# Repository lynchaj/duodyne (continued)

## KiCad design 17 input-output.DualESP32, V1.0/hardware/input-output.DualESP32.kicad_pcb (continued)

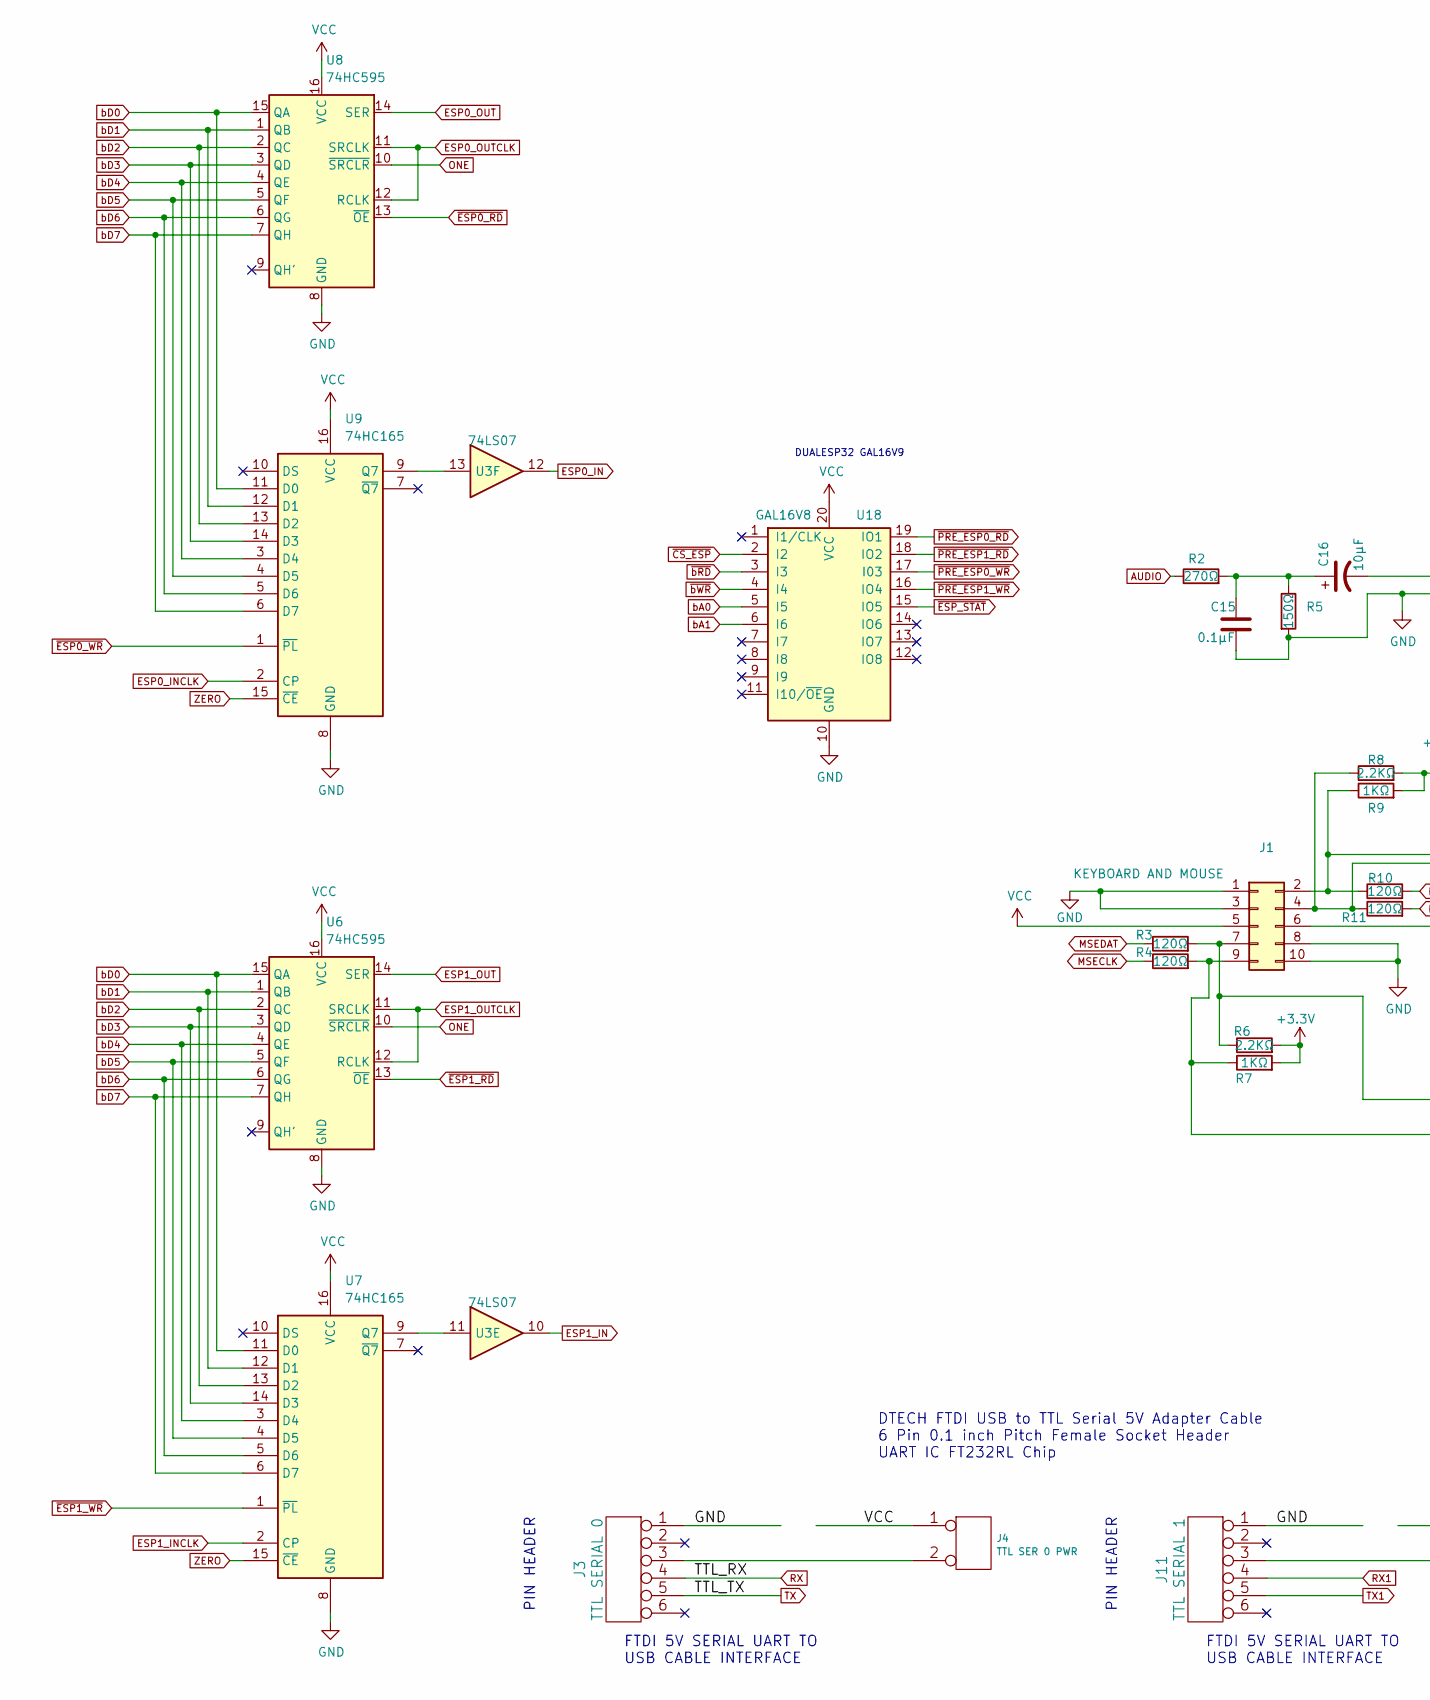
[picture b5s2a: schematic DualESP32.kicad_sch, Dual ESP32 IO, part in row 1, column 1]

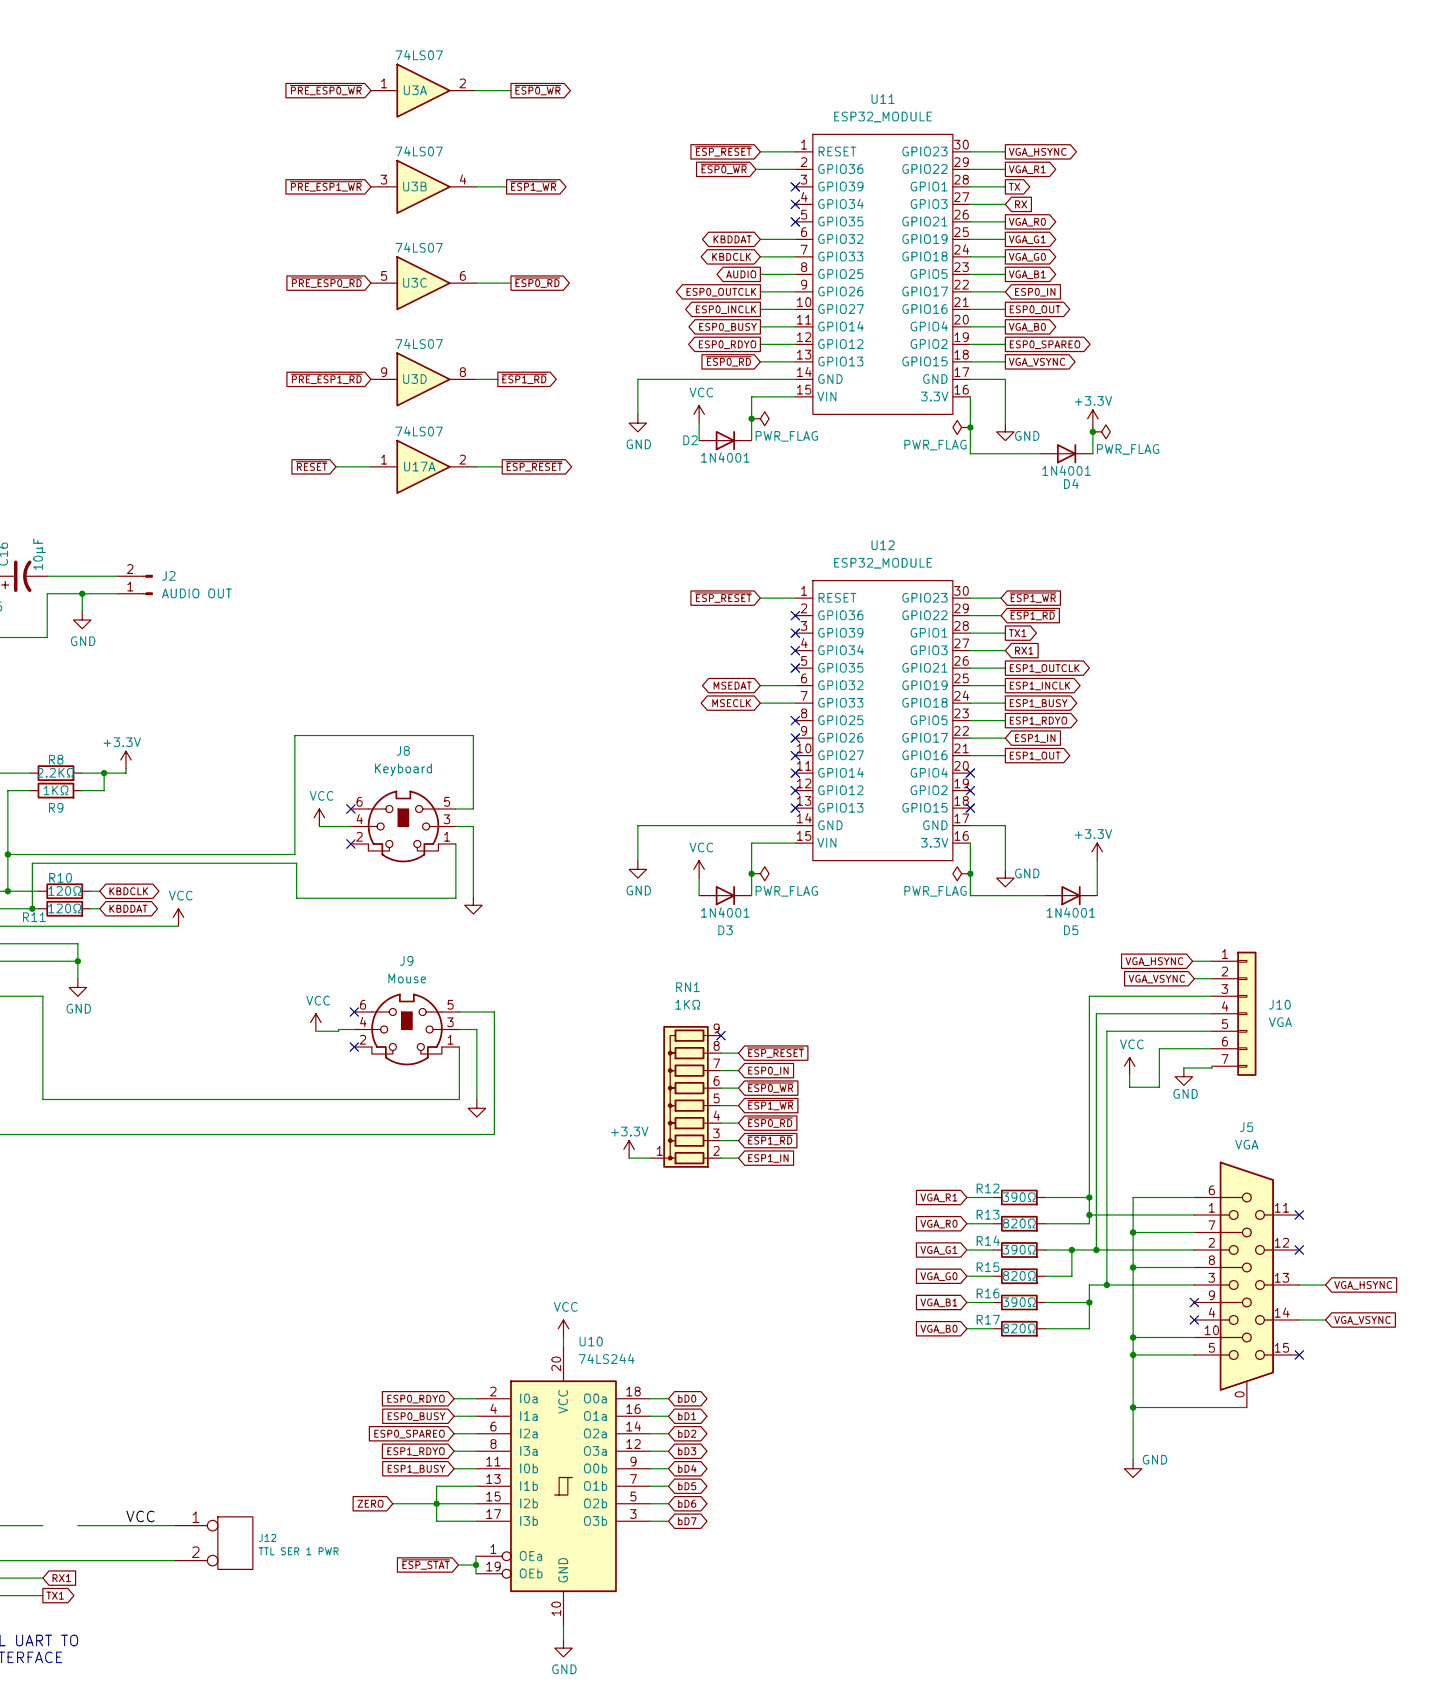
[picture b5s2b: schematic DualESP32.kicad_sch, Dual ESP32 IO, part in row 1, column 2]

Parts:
C15: 0.1µF; C_Disc_D5.0mm_W2.5mm_P5.00mm
C16: 10µF; CP_Radial_D5.0mm_P2.50mm
D2, D3, D4, D5: 1N4001; D_DO-41_SOD81_P10.16mm_Horizontal
J1: KEYBOARD AND MOUSE; PinHeader_2x05_P2.54mm_Horizontal
J2: AUDIO OUT; PinHeader_1x02_P2.54mm_Horizontal
J3: TTL SERIAL 0; PinHeader_1x06_P2.54mm_Horizontal
J4: TTL SER 0 PWR; PinHeader_1x02_P2.54mm_Vertical
J5: VGA; DSUB-15-HD_Female_Horizontal_P2.29x1.98mm_EdgePinOffset3.03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
J8: Keyboard; mini_din
J9: Mouse; mini_din
J10: VGA; PinHeader_1x07_P2.54mm_Horizontal
J11: TTL SERIAL 1; PinHeader_1x06_P2.54mm_Horizontal
J12: TTL SER 1 PWR; PinHeader_1x02_P2.54mm_Vertical
R2: 270Ω; R_Axial_DIN0207_L6.3mm_D2.5mm_P7.62mm_Horizontal
R3, R4, R10, R11: 120Ω; R_Axial_DIN0207_L6.3mm_D2.5mm_P7.62mm_Horizontal
R5: 150Ω; R_Axial_DIN0207_L6.3mm_D2.5mm_P7.62mm_Horizontal
R6, R8: 2.2KΩ; R_Axial_DIN0207_L6.3mm_D2.5mm_P7.62mm_Horizontal
R7, R9: 1KΩ; R_Axial_DIN0207_L6.3mm_D2.5mm_P7.62mm_Horizontal
R12, R14, R16: 390Ω; R_Axial_DIN0207_L6.3mm_D2.5mm_P7.62mm_Horizontal
R13, R15, R17: 820Ω; R_Axial_DIN0207_L6.3mm_D2.5mm_P7.62mm_Horizontal
RN1: 1KΩ; R_Array_SIP9
U3, U17: 74LS07; DIP-14_W7.62mm
U6, U8: 74HC595; DIP-16_W7.62mm
U7, U9: 74HC165; DIP-16_W7.62mm
U10: 74LS244; DIP-20_W7.62mm
U11, U12: ESP32_MODULE
U18: GAL16V8; DIP-20_W7.62mm

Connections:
+3.3V: D4.1 (K), D5.1 (K), R6.2, R7.2, R8.2, R9.2, RN1.1 (common)
AUDIO: R2.1, U11.8 (GPIO25)
ESP0_BUSY: U10.4 (I1a), U11.11 (GPIO14)
ESP0_IN: RN1.7 (R6), U3.12, U11.22 (GPIO17)
ESP0_INCLK: U9.2 (CP), U11.10 (GPIO27)
ESP0_OUT: U8.14 (SER), U11.21 (GPIO16)
ESP0_OUTCLK: U8.11 (SRCLK), U8.12 (RCLK), U11.9 (GPIO26)
ESP0_RDYO: U10.2 (I0a), U11.12 (GPIO12)
ESP0_SPAREO: U10.6 (I2a), U11.19 (GPIO2)
ESP1_BUSY: U10.11 (I0b), U12.24 (GPIO18)
ESP1_IN: RN1.2 (R1), U3.10, U12.22 (GPIO17)
ESP1_INCLK: U7.2 (CP), U12.25 (GPIO19)
ESP1_OUT: U6.14 (SER), U12.21 (GPIO16)
ESP1_OUTCLK: U6.11 (SRCLK), U6.12 (RCLK), U12.26 (GPIO21)
ESP1_RDYO: U10.8 (I3a), U12.23 (GPIO5)
GND: C15.2, J1.1, J1.3, J1.8, J1.10, J2.1, J3.1, J5.0, J5.5, J5.6, J5.7, J5.8, J5.10, J8.3, J8.SH1, J8.SH2, J8.SH3, J9.3, J9.SH1, J9.SH2, J9.SH3, J10.7, J11.1, R5.2, U6.8 (GND), U7.8 (GND), U8.8 (GND), U9.8 (GND), U10.10 (GND), U11.14 (GND), U11.17 (GND), U12.14 (GND), U12.17 (GND), U18.10 (GND); also elsewhere on the board
KBDCLK: R10.2, U11.7 (GPIO33)
KBDDAT: R11.2, U11.6 (GPIO32)
MSECLK: R4.1, U12.7 (GPIO33)
MSEDAT: R3.1, U12.6 (GPIO32)
unnamed: C15.1, C16.1, R2.2, R5.1
unnamed: C16.2, J2.2
unnamed: D2.1 (K), U11.15 (VIN)
unnamed: D3.1 (K), U12.15 (VIN)
unnamed: D4.2 (A), U11.16 (3.3V)
unnamed: D5.2 (A), U12.16 (3.3V)
unnamed: J1.2, J8.5, R9.1, R10.1
unnamed: J1.4, J8.1, R8.1, R11.1
unnamed: J1.7, J9.1, R3.2, R6.1
unnamed: J1.9, J9.5, R4.2, R7.1
unnamed: J3.3, J4.2 (PM)
unnamed: J5.1, J10.3, R12.2, R13.2
unnamed: J5.2, J10.4, R14.2, R15.2
unnamed: J5.3, J10.5, R16.2, R17.2
unnamed: J11.3, J12.2 (PM)
unnamed: U3.11, U7.9 (Q7)
unnamed: U3.13, U9.9 (Q7)
ONE: U6.10 (~SRCLR), U8.10 (~SRCLR); also elsewhere on the board
RX: J3.4, U11.27 (GPIO3)
RX1: J11.4, U12.27 (GPIO3)
TX: J3.5, U11.28 (GPIO1)
TX1: J11.5, U12.28 (GPIO1)
VCC: D2.2 (A), D3.2 (A), J1.5, J1.6, J4.1, J8.4, J9.4, J10.6, J12.1, U6.16 (VCC), U7.16 (VCC), U8.16 (VCC), U9.16 (VCC), U10.20 (VCC), U18.20 (VCC); also elsewhere on the board
VGA_B0: R17.1, U11.20 (GPIO4)
VGA_B1: R16.1, U11.23 (GPIO5)
VGA_G0: R15.1, U11.24 (GPIO18)
VGA_G1: R14.1, U11.25 (GPIO19)
VGA_HSYNC: J5.13, J10.1, U11.30 (GPIO23)
VGA_R0: R13.1, U11.26 (GPIO21)
VGA_R1: R12.1, U11.29 (GPIO22)
VGA_VSYNC: J5.14, J10.2, U11.18 (GPIO15)
ZERO: U7.15 (~CE), U9.15 (~CE), U10.13 (I1b), U10.15 (I2b), U10.17 (I3b); also elsewhere on the board
bA0: U18.5 (I5); also elsewhere on the board
bA1: U18.6 (I6); also elsewhere on the board
bD0: U6.15 (QA), U7.11 (D0), U8.15 (QA), U9.11 (D0), U10.18 (O0a); also elsewhere on the board
bD1: U6.1 (QB), U7.12 (D1), U8.1 (QB), U9.12 (D1), U10.16 (O1a); also elsewhere on the board
bD2: U6.2 (QC), U7.13 (D2), U8.2 (QC), U9.13 (D2), U10.14 (O2a); also elsewhere on the board
bD3: U6.3 (QD), U7.14 (D3), U8.3 (QD), U9.14 (D3), U10.12 (O3a); also elsewhere on the board
bD4: U6.4 (QE), U7.3 (D4), U8.4 (QE), U9.3 (D4), U10.9 (O0b); also elsewhere on the board
bD5: U6.5 (QF), U7.4 (D5), U8.5 (QF), U9.4 (D5), U10.7 (O1b); also elsewhere on the board
bD6: U6.6 (QG), U7.5 (D6), U8.6 (QG), U9.5 (D6), U10.5 (O2b); also elsewhere on the board
bD7: U6.7 (QH), U7.6 (D7), U8.7 (QH), U9.6 (D7), U10.3 (O3b); also elsewhere on the board
~CS_ESP: U18.2 (I2); also elsewhere on the board
~ESP0_RD: RN1.4 (R3), U3.6, U8.13 (~OE), U11.13 (GPIO13)
~ESP0_WR: RN1.6 (R5), U3.2, U9.1 (~PL), U11.2 (GPIO36)
~ESP1_RD: RN1.3 (R2), U3.8, U6.13 (~OE), U12.29 (GPIO22)
~ESP1_WR: RN1.5 (R4), U3.4, U7.1 (~PL), U12.30 (GPIO23)
~ESP_RESET: RN1.8 (R7), U11.1 (RESET), U12.1 (RESET), U17.2
~ESP_STAT: U10.1 (OEa), U10.19 (OEb), U18.15 (IO5)
~PRE_ESP0_RD: U3.5, U18.19 (IO1)
~PRE_ESP0_WR: U3.1, U18.17 (I03)
~PRE_ESP1_RD: U3.9, U18.18 (IO2)
~PRE_ESP1_WR: U3.3, U18.16 (IO4)
~RESET: U17.1; also elsewhere on the board
~bRD: U18.3 (I3); also elsewhere on the board
~bWR: U18.4 (I4); also elsewhere on the board

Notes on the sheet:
FTDI 5V SERIAL UART TO USB CABLE INTERFACE
PIN HEADER
DTECH FTDI USB to TTL Serial 5V Adapter Cable 6 Pin 0.1 inch Pitch Female Socket Header UART IC FT232RL Chip
DUALESP32 GAL16V9

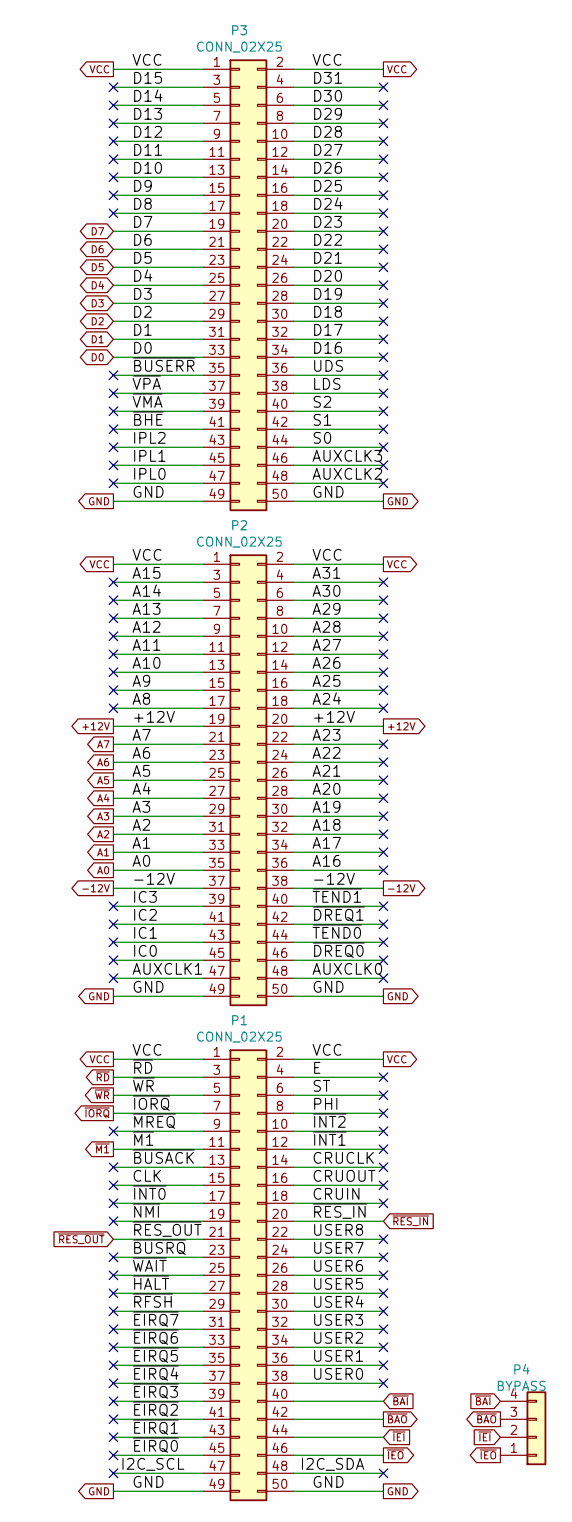
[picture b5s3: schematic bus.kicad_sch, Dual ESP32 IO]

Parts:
P1, P2, P3: CONN_02X25; IDC-Header_2x25_P2.54mm_Horizontal
P4: BYPASS; PinHeader_1x04_P2.54mm_Vertical

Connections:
+12V: P2.19, P2.20
-12V: P2.37, P2.38
/bus/A8: P2.17
/bus/A9: P2.15
/bus/A10: P2.13
/bus/A11: P2.11
/bus/A12: P2.9
/bus/A13: P2.7
/bus/A14: P2.5
/bus/A15: P2.3
/bus/A16: P2.36
/bus/A17: P2.34
/bus/A18: P2.32
/bus/A19: P2.30
/bus/A20: P2.28
/bus/A21: P2.26
/bus/A22: P2.24
/bus/A23: P2.22
/bus/A24: P2.18
/bus/A25: P2.16
/bus/A26: P2.14
/bus/A27: P2.12
/bus/A28: P2.10
/bus/A29: P2.8
/bus/A30: P2.6
/bus/A31: P2.4
/bus/AUXCLK0: P2.48
/bus/AUXCLK1: P2.47
/bus/AUXCLK2: P3.48
/bus/AUXCLK3: P3.46
/bus/CLK: P1.15
/bus/CRUCLK: P1.14
/bus/CRUIN: P1.18
/bus/CRUOUT: P1.16
/bus/D8: P3.17
/bus/D9: P3.15
/bus/D10: P3.13
/bus/D11: P3.11
/bus/D12: P3.9
/bus/D13: P3.7
/bus/D14: P3.5
/bus/D15: P3.3
/bus/D16: P3.34
/bus/D17: P3.32
/bus/D18: P3.30
/bus/D19: P3.28
/bus/D20: P3.26
/bus/D21: P3.24
/bus/D22: P3.22
/bus/D23: P3.20
/bus/D24: P3.18
/bus/D25: P3.16
/bus/D26: P3.14
/bus/D27: P3.12
/bus/D28: P3.10
/bus/D29: P3.8
/bus/D30: P3.6
/bus/D31: P3.4
/bus/E: P1.4
/bus/I2C_SCL: P1.47
/bus/I2C_SDA: P1.48
/bus/IC0: P2.45
/bus/IC1: P2.43
/bus/IC2: P2.41
/bus/IC3: P2.39
/bus/IPL0: P3.47
/bus/IPL1: P3.45
/bus/IPL2: P3.43
/bus/LDS: P3.38
/bus/PHI: P1.8
/bus/S0: P3.44
/bus/S1: P3.42
/bus/S2: P3.40
/bus/ST: P1.6
/bus/UDS: P3.36
/bus/USER0: P1.38
/bus/USER1: P1.36
/bus/USER2: P1.34
/bus/USER3: P1.32
/bus/USER4: P1.30
/bus/USER5: P1.28
/bus/USER6: P1.26
/bus/USER7: P1.24
/bus/USER8: P1.22
/bus/~BHE: P3.41
/bus/~BUSACK: P1.13
/bus/~BUSERR: P3.35
/bus/~BUSRQ: P1.23
/bus/~DREQ0: P2.46
/bus/~DREQ1: P2.42
/bus/~EIRQ0: P1.45
/bus/~EIRQ1: P1.43
/bus/~EIRQ2: P1.41
/bus/~EIRQ3: P1.39
/bus/~EIRQ4: P1.37
/bus/~EIRQ5: P1.35
/bus/~EIRQ6: P1.33
/bus/~EIRQ7: P1.31
/bus/~HALT: P1.27
/bus/~INT0: P1.17
/bus/~INT1: P1.12
/bus/~INT2: P1.10
/bus/~MREQ: P1.9
/bus/~NMI: P1.19
/bus/~RFSH: P1.29
/bus/~TEND0: P2.44
/bus/~TEND1: P2.40
/bus/~VMA: P3.39
/bus/~VPA: P3.37
/bus/~WAIT: P1.25
A0: P2.35; also elsewhere on the board
A1: P2.33; also elsewhere on the board
A2: P2.31; also elsewhere on the board
A3: P2.29; also elsewhere on the board
A4: P2.27; also elsewhere on the board
A5: P2.25; also elsewhere on the board
A6: P2.23; also elsewhere on the board
A7: P2.21; also elsewhere on the board
D0: P3.33; also elsewhere on the board
D1: P3.31; also elsewhere on the board
D2: P3.29; also elsewhere on the board
D3: P3.27; also elsewhere on the board
D4: P3.25; also elsewhere on the board
D5: P3.23; also elsewhere on the board
D6: P3.21; also elsewhere on the board
D7: P3.19; also elsewhere on the board
GND: P1.49, P1.50, P2.49, P2.50, P3.49, P3.50; also elsewhere on the board
VCC: P1.1, P1.2, P2.1, P2.2, P3.1, P3.2; also elsewhere on the board
~BAI: P1.40, P4.4
~BAO: P1.42, P4.3
~IEI: P1.44, P4.2
~IEO: P1.46, P4.1
~IORQ: P1.7; also elsewhere on the board
~M1: P1.11; also elsewhere on the board
~RD: P1.3; also elsewhere on the board
~RES_IN: P1.20; also elsewhere on the board
~RES_OUT: P1.21; also elsewhere on the board
~WR: P1.5; also elsewhere on the board

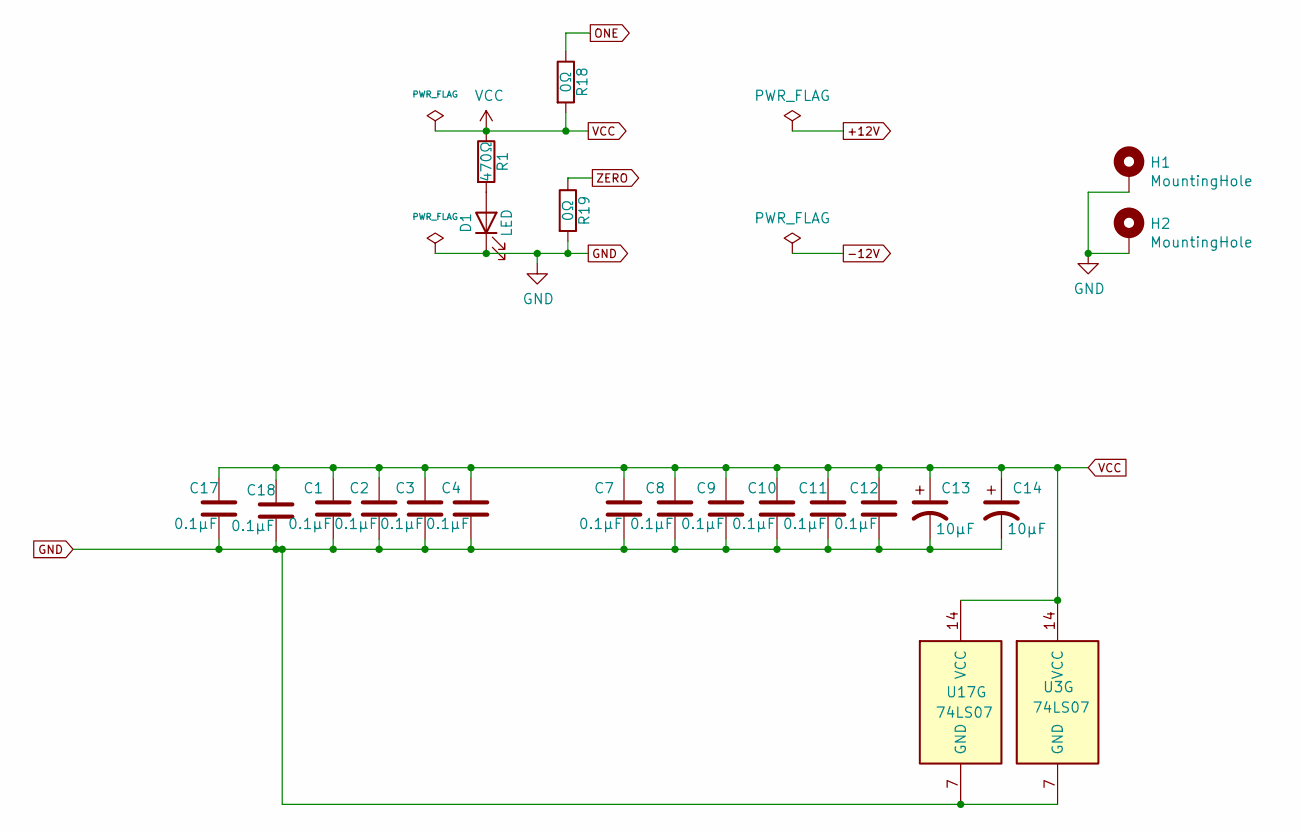
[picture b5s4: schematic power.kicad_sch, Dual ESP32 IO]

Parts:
C1, C2, C3, C4, C7, C8, C9, C10, C11, C12, C17, C18: 0.1µF; C_Disc_D5.0mm_W2.5mm_P5.00mm
C13, C14: 10µF; CP_Radial_D5.0mm_P2.50mm
D1: LED; LED_D3.0mm_Horizontal_O3.81mm_Z2.0mm
H1, H2: MountingHole; MountingHole_3.2mm_M3_Pad
R1: 470Ω; R_Axial_DIN0207_L6.3mm_D2.5mm_P7.62mm_Horizontal
R18, R19: 0Ω; R_Axial_DIN0207_L6.3mm_D2.5mm_P7.62mm_Horizontal
U3, U17: 74LS07; DIP-14_W7.62mm

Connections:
GND: C1.2, C2.2, C3.2, C4.2, C7.2, C8.2, C9.2, C10.2, C11.2, C12.2, C13.2, C14.2, C17.2, C18.2, D1.1 (K), H1.1, H2.1, R19.2, U3.7 (GND), U17.7 (GND); also elsewhere on the board
unnamed: D1.2 (A), R1.2
ONE: R18.1; also elsewhere on the board
VCC: C1.1, C2.1, C3.1, C4.1, C7.1, C8.1, C9.1, C10.1, C11.1, C12.1, C13.1, C14.1, C17.1, C18.1, R1.1, R18.2, U3.14 (VCC), U17.14 (VCC); also elsewhere on the board
ZERO: R19.1; also elsewhere on the board

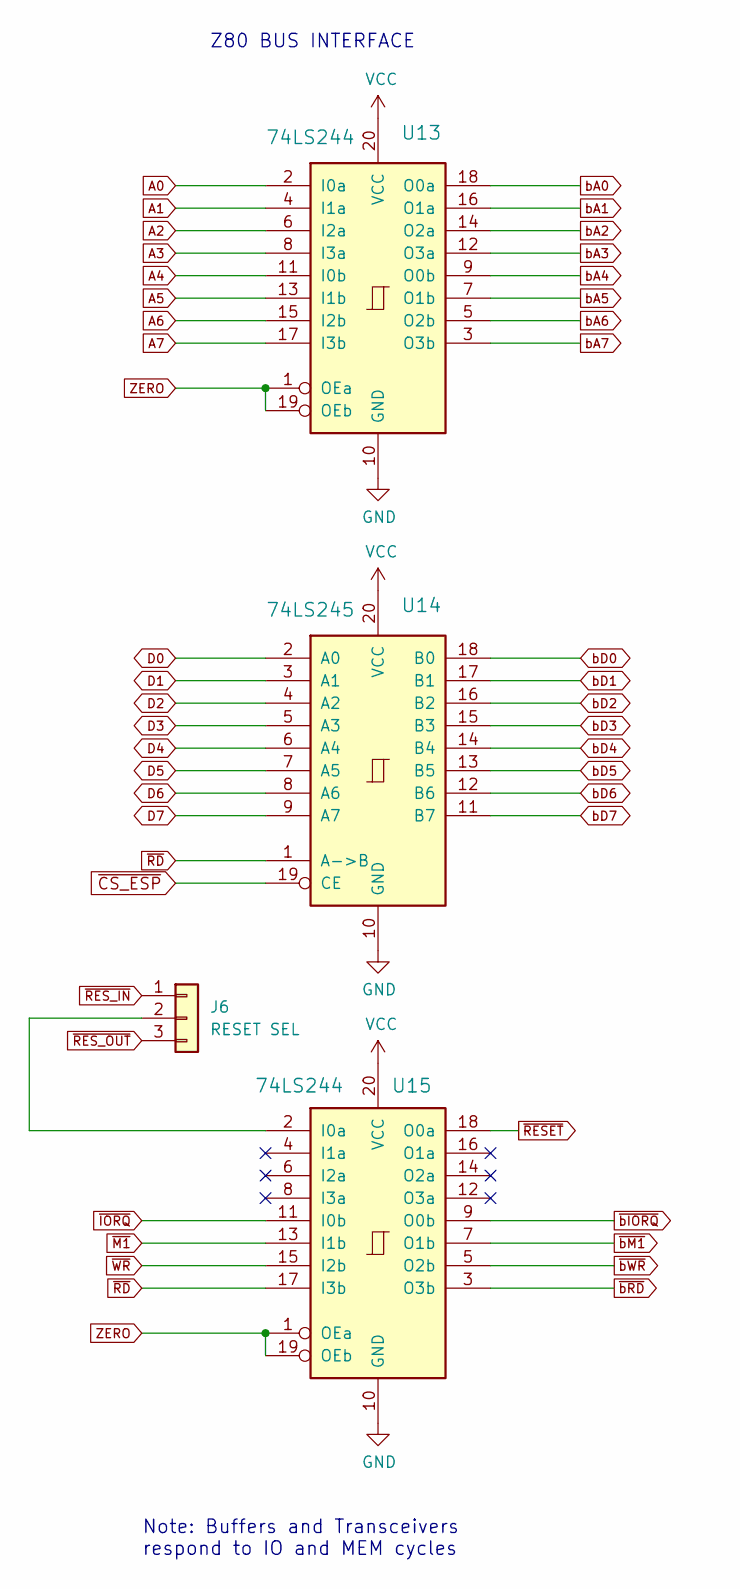
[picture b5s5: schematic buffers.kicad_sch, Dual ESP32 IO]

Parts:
J6: RESET SEL; PinHeader_1x03_P2.54mm_Vertical
U13, U15: 74LS244; DIP-20_W7.62mm
U14: 74LS245; DIP-20_W7.62mm

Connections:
A0: U13.2 (I0a); also elsewhere on the board
A1: U13.4 (I1a); also elsewhere on the board
A2: U13.6 (I2a); also elsewhere on the board
A3: U13.8 (I3a); also elsewhere on the board
A4: U13.11 (I0b); also elsewhere on the board
A5: U13.13 (I1b); also elsewhere on the board
A6: U13.15 (I2b); also elsewhere on the board
A7: U13.17 (I3b); also elsewhere on the board
D0: U14.2 (A0); also elsewhere on the board
D1: U14.3 (A1); also elsewhere on the board
D2: U14.4 (A2); also elsewhere on the board
D3: U14.5 (A3); also elsewhere on the board
D4: U14.6 (A4); also elsewhere on the board
D5: U14.7 (A5); also elsewhere on the board
D6: U14.8 (A6); also elsewhere on the board
D7: U14.9 (A7); also elsewhere on the board
GND: U13.10 (GND), U14.10 (GND), U15.10 (GND); also elsewhere on the board
unnamed: J6.2, U15.2 (I0a)
VCC: U13.20 (VCC), U14.20 (VCC), U15.20 (VCC); also elsewhere on the board
ZERO: U13.1 (OEa), U13.19 (OEb), U15.1 (OEa), U15.19 (OEb); also elsewhere on the board
bA0: U13.18 (O0a); also elsewhere on the board
bA1: U13.16 (O1a); also elsewhere on the board
bA2: U13.14 (O2a); also elsewhere on the board
bA3: U13.12 (O3a); also elsewhere on the board
bA4: U13.9 (O0b); also elsewhere on the board
bA5: U13.7 (O1b); also elsewhere on the board
bA6: U13.5 (O2b); also elsewhere on the board
bA7: U13.3 (O3b); also elsewhere on the board
bD0: U14.18 (B0); also elsewhere on the board
bD1: U14.17 (B1); also elsewhere on the board
bD2: U14.16 (B2); also elsewhere on the board
bD3: U14.15 (B3); also elsewhere on the board
bD4: U14.14 (B4); also elsewhere on the board
bD5: U14.13 (B5); also elsewhere on the board
bD6: U14.12 (B6); also elsewhere on the board
bD7: U14.11 (B7); also elsewhere on the board
~CS_ESP: U14.19 (CE); also elsewhere on the board
~IORQ: U15.11 (I0b); also elsewhere on the board
~M1: U15.13 (I1b); also elsewhere on the board
~RD: U14.1 (A->B), U15.17 (I3b); also elsewhere on the board
~RESET: U15.18 (O0a); also elsewhere on the board
~RES_IN: J6.1; also elsewhere on the board
~RES_OUT: J6.3; also elsewhere on the board
~WR: U15.15 (I2b); also elsewhere on the board
~bIORQ: U15.9 (O0b); also elsewhere on the board
~bM1: U15.7 (O1b); also elsewhere on the board
~bRD: U15.3 (O3b); also elsewhere on the board
~bWR: U15.5 (O2b); also elsewhere on the board

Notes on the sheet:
Note: Buffers and Transceivers respond to IO and MEM cycles
Z80 BUS INTERFACE

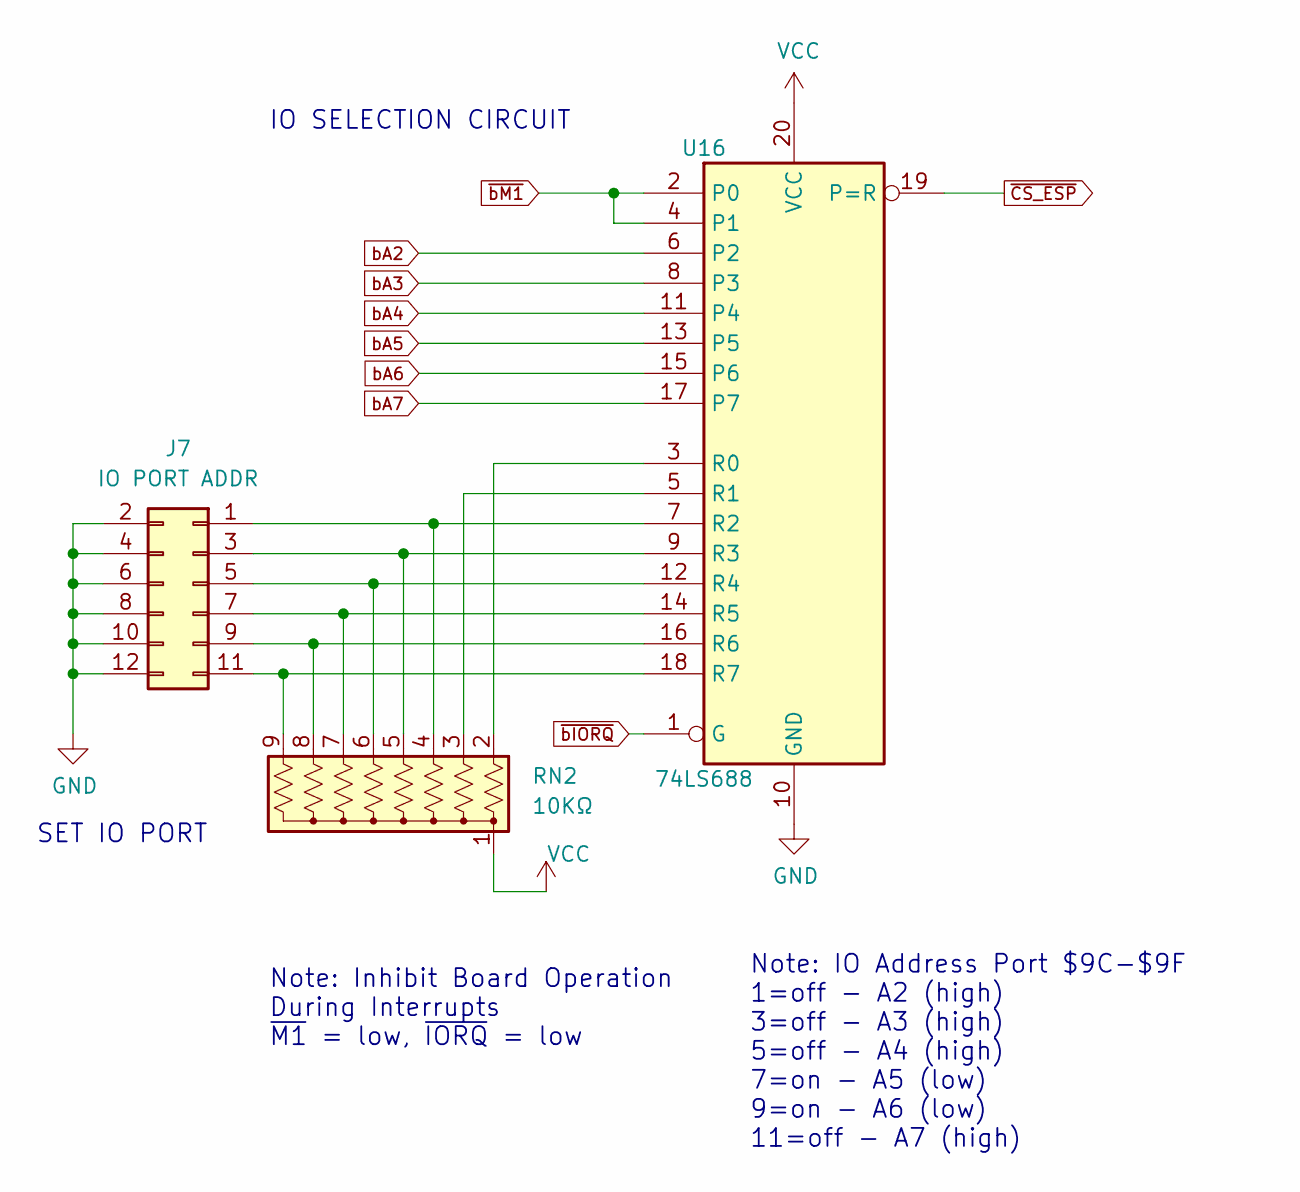
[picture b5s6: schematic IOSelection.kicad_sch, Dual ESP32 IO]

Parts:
J7: IO PORT ADDR; PinHeader_2x06_P2.54mm_Vertical
RN2: 10KΩ; R_Array_SIP9
U16: 74LS688; DIP-20_W7.62mm

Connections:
GND: J7.2, J7.4, J7.6, J7.8, J7.10, J7.12, U16.10 (GND); also elsewhere on the board
unnamed: J7.1, RN2.4 (R3), U16.7 (R2)
unnamed: J7.3, RN2.5 (R4), U16.9 (R3)
unnamed: J7.5, RN2.6 (R5), U16.12 (R4)
unnamed: J7.7, RN2.7 (R6), U16.14 (R5)
unnamed: J7.9, RN2.8 (R7), U16.16 (R6)
unnamed: J7.11, RN2.9 (R8), U16.18 (R7)
unnamed: RN2.2 (R1), U16.3 (R0)
unnamed: RN2.3 (R2), U16.5 (R1)
VCC: RN2.1 (common), U16.20 (VCC); also elsewhere on the board
bA2: U16.6 (P2); also elsewhere on the board
bA3: U16.8 (P3); also elsewhere on the board
bA4: U16.11 (P4); also elsewhere on the board
bA5: U16.13 (P5); also elsewhere on the board
bA6: U16.15 (P6); also elsewhere on the board
bA7: U16.17 (P7); also elsewhere on the board
~CS_ESP: U16.19 (P=R); also elsewhere on the board
~bIORQ: U16.1 (G); also elsewhere on the board
~bM1: U16.2 (P0), U16.4 (P1); also elsewhere on the board

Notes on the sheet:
Note: Inhibit Board Operation During Interrupts ~{M1} = low, ~{IORQ} = low
Note: IO Address Port $9C-$9F 1=off - A2 (high) 3=off - A3 (high) 5=off - A4 (high) 7=on - A5 (low) 9=on - A6 (low) 11=off - A7 (high)
SET IO PORT
IO SELECTION CIRCUIT

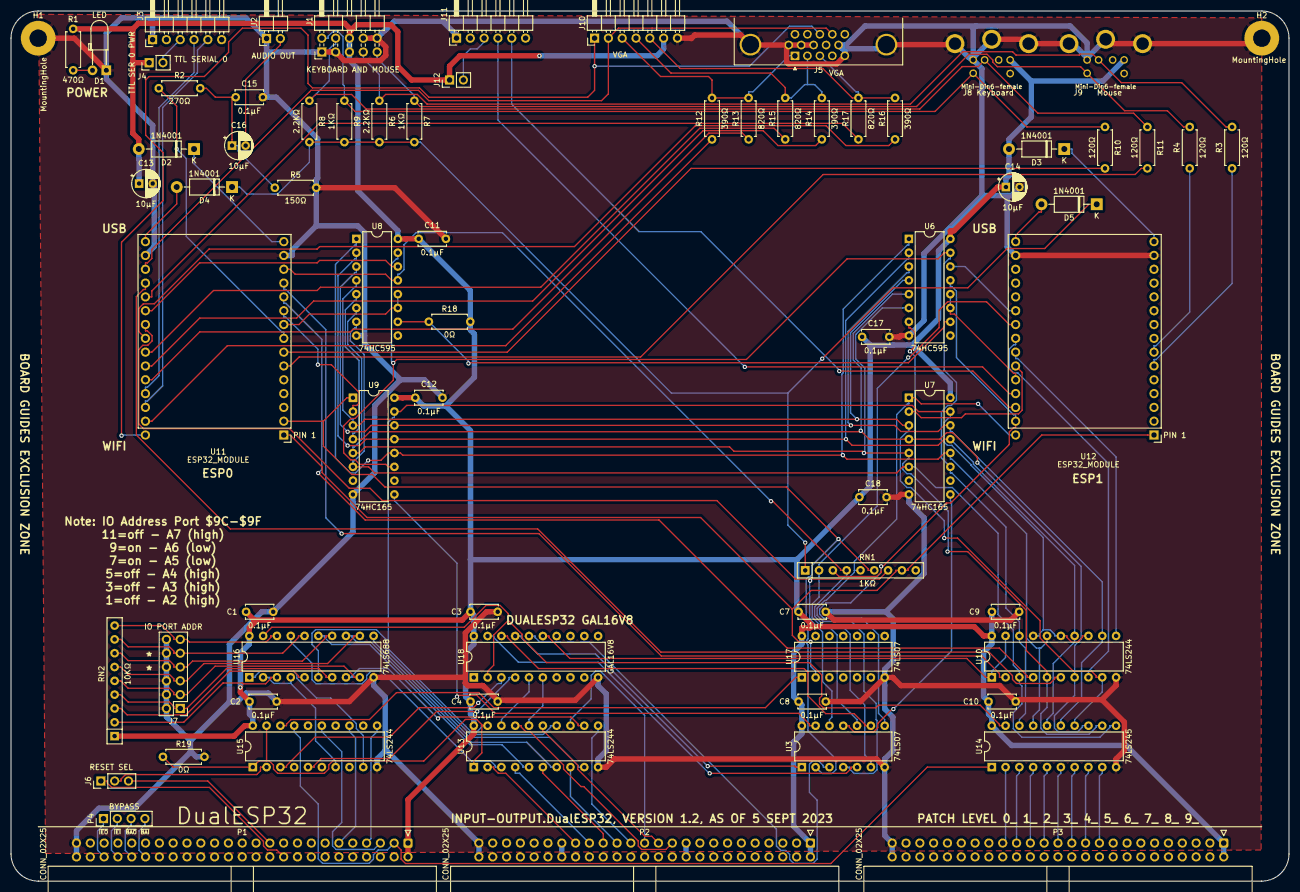
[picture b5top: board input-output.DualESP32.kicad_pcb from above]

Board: 2 copper layers, 235.0 x 160.0 mm, 74 parts (0 on the bottom side), 122 nets.
